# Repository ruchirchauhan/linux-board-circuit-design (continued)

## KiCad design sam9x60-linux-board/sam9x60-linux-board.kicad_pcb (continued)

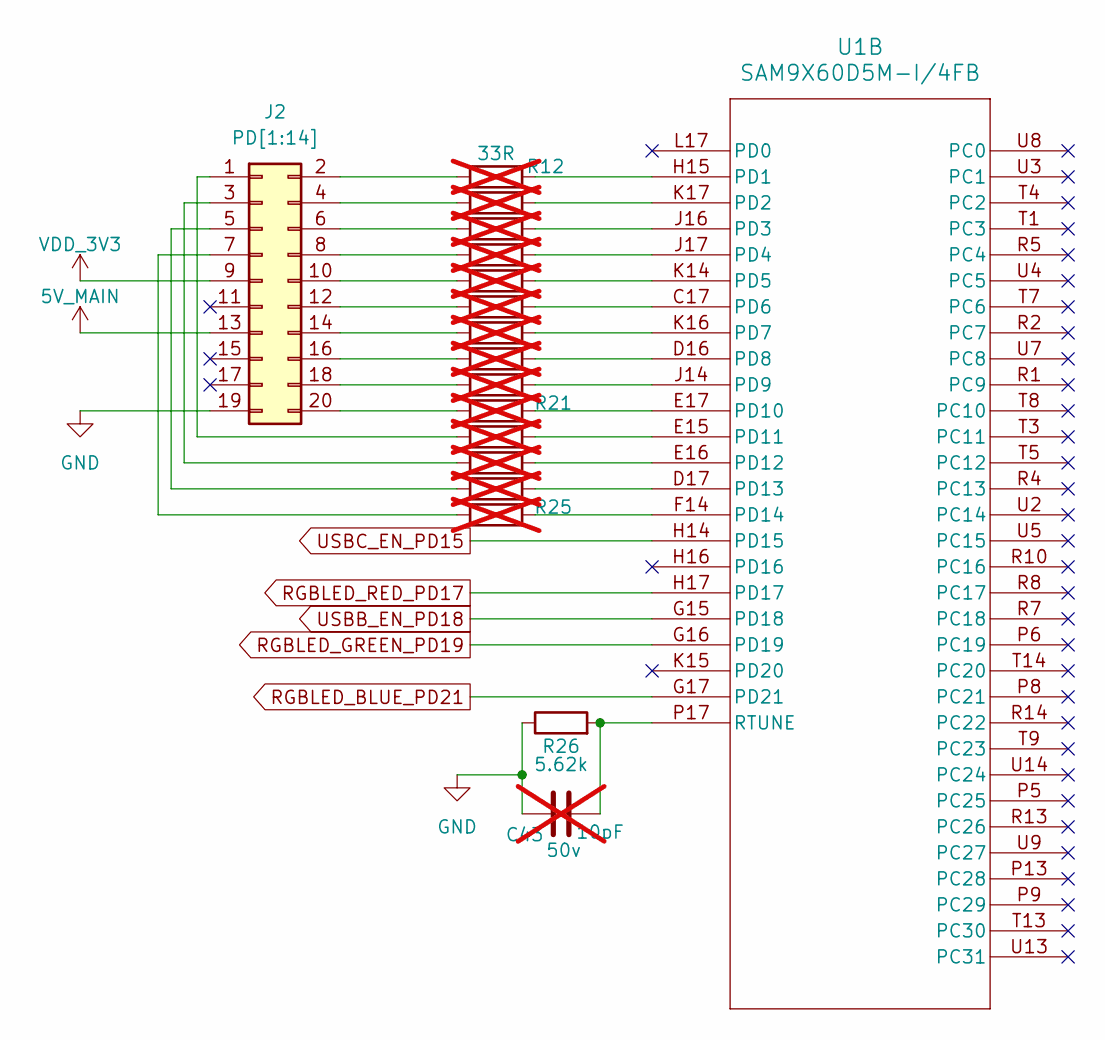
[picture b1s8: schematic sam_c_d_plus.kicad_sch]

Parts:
C43: 10pF; C_0805_2012Metric; Voltage 50v; not fitted
J2: PD[1:14]; PinHeader_2x10_P2.54mm_Vertical
R12, R13, R14, R15, R16, R17, R18, R19, R20, R21, R22, R23, R24, R25: 33R; R_0603_1608Metric; not fitted
R26: 5.62k; R_0603_1608Metric
U1: SAM9X60D5M-I/4FB; TFBGA233_4FB_MCH

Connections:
5V_MAIN: J2.13; also elsewhere on the board
/sam_a_b_plus/DDRCAL: U1.C8 (DDR_CAL); also elsewhere on the board
/sam_a_b_plus/XIN24M: U1.T11 (XIN); also elsewhere on the board
/sam_a_b_plus/XIN32K: U1.U10 (XIN32); also elsewhere on the board
/sam_a_b_plus/XOUT24M: U1.U11 (XOUT); also elsewhere on the board
/sam_a_b_plus/XOUT32K: U1.T10 (XOUT32); also elsewhere on the board
DBGU_RX_PA9: U1.N2 (PA9); also elsewhere on the board
DBGU_TX_PA10: U1.M4 (PA10); also elsewhere on the board
EEPROM_TWCK_PA1: U1.L3 (PA1); also elsewhere on the board
EEPROM_TWD_PA0: U1.L2 (PA0); also elsewhere on the board
ETH0_IRQ_PB8: U1.D5 (PB8); also elsewhere on the board
ETH0_MDC_PB6: U1.D3 (PB6); also elsewhere on the board
ETH0_MDIO_PB5: U1.E1 (PB5); also elsewhere on the board
ETH0_NRST_PB16: U1.E2 (PB16); also elsewhere on the board
ETH0_RX0_PB0: U1.B3 (PB0); also elsewhere on the board
ETH0_RX1_PB1: U1.D1 (PB1); also elsewhere on the board
ETH0_RXDV_PB3: U1.D2 (PB3); also elsewhere on the board
ETH0_RXER_PB2: U1.A3 (PB2); also elsewhere on the board
ETH0_TX0_PB9: U1.B4 (PB9); also elsewhere on the board
ETH0_TX1_PB10: U1.B5 (PB10); also elsewhere on the board
ETH0_TXCK_PB4: U1.E3 (PB4); also elsewhere on the board
ETH0_TXEN_PB7: U1.F4 (PB7); also elsewhere on the board
FCOM1_UART_RX_PA6: U1.N1 (PA6); also elsewhere on the board
FCOM1_UART_TX_PA5: U1.N3 (PA5); also elsewhere on the board
FCOM5_SPI_CK_PA23: U1.C11 (PA23); also elsewhere on the board
FCOM5_SPI_MISO_PA21: U1.B11 (PA21); also elsewhere on the board
FCOM5_SPI_MOSI_PA22: U1.A10 (PA22); also elsewhere on the board
FCOM5_SPI_NPCS0_PA8: U1.P3 (PA8); also elsewhere on the board
FCOM5_SPI_NPCS1_PA7: U1.P2 (PA7); also elsewhere on the board
FCOM5_SPI_NPCS2_PA31: U1.H2 (PA31); also elsewhere on the board
FCOM5_SPI_NPCS3_PA30: U1.H1 (PA30); also elsewhere on the board
FCOM12_I2C_TWCK_PB22: U1.B8 (PB22); also elsewhere on the board
FCOM12_I2C_TWD_PB21: U1.A8 (PB21); also elsewhere on the board
GND: C43.1, J2.19, R26.1, U1.N7 (GNDIN33), U1.P7 (GNDIN33); also elsewhere on the board
MCP16501_LPM_PB15: U1.C4 (PB15); also elsewhere on the board
MPU_NRSTOUT_PB25: U1.B7 (PB25); also elsewhere on the board
NRST: U1.P1 (NRST); also elsewhere on the board
unnamed: J2.1, R22.1
unnamed: J2.2, R12.1
unnamed: J2.3, R23.1
unnamed: J2.4, R13.1
unnamed: J2.5, R24.1
unnamed: J2.6, R14.1
unnamed: J2.7, R25.1
unnamed: J2.8, R15.1
unnamed: J2.10, R16.1
unnamed: J2.12, R17.1
unnamed: J2.14, R18.1
unnamed: J2.16, R19.1
unnamed: J2.18, R20.1
unnamed: J2.20, R21.1
unnamed 76: U1.P11 (VDDOUT25); also elsewhere on the board
unnamed: R12.2, U1.H15 (PD1)
unnamed: R13.2, U1.K17 (PD2)
unnamed: R14.2, U1.J16 (PD3)
unnamed: R15.2, U1.J17 (PD4)
unnamed: R16.2, U1.K14 (PD5)
unnamed: R17.2, U1.C17 (PD6)
unnamed: R18.2, U1.K16 (PD7)
unnamed: R19.2, U1.D16 (PD8)
unnamed: R20.2, U1.J14 (PD9)
unnamed: R21.2, U1.E17 (PD10)
unnamed: R22.2, U1.E15 (PD11)
unnamed: R23.2, U1.E16 (PD12)
unnamed: R24.2, U1.D17 (PD13)
unnamed: R25.2, U1.F14 (PD14)
unnamed: C43.2, R26.2, U1.P17 (RTUNE)
RGBLED_BLUE_PD21: U1.G17 (PD21); also elsewhere on the board
RGBLED_GREEN_PD19: U1.G16 (PD19); also elsewhere on the board
RGBLED_RED_PD17: U1.H17 (PD17); also elsewhere on the board
RTCK: U1.N4 (RTCK); also elsewhere on the board
SDMMC0_CD_PA25: U1.A9 (PA25); also elsewhere on the board
SDMMC0_CK_PA17: U1.H4 (PA17); also elsewhere on the board
SDMMC0_CMD_PA16: U1.J2 (PA16); also elsewhere on the board
SDMMC0_DAT0_PA15: U1.K1 (PA15); also elsewhere on the board
SDMMC0_DAT1_PA18: U1.H3 (PA18); also elsewhere on the board
SDMMC0_DAT2_PA19: U1.J1 (PA19); also elsewhere on the board
SDMMC0_DAT3_PA20: U1.J4 (PA20); also elsewhere on the board
SHDN: U1.N17 (SHDN); also elsewhere on the board
TCK: U1.P12 (TCK); also elsewhere on the board
TDI: U1.L15 (TDI); also elsewhere on the board
TDO: U1.N15 (TDO); also elsewhere on the board
TMS: U1.N16 (TMS); also elsewhere on the board
USBA_N: U1.U16 (HSDMA); also elsewhere on the board
USBA_P: U1.T15 (HSDPA); also elsewhere on the board
USBA_VBUS_DETECT_PA27: U1.D12 (PA27); also elsewhere on the board
USBB_EN_PD18: U1.G15 (PD18); also elsewhere on the board
USBB_N: U1.R17 (HSDMB); also elsewhere on the board
USBB_OVCUR_PA26: U1.D10 (PA26); also elsewhere on the board
USBB_P: U1.T17 (HSDPB); also elsewhere on the board
USBC_EN_PD15: U1.H14 (PD15); also elsewhere on the board
USBC_N: U1.P15 (HSDMC); also elsewhere on the board
USBC_OVCUR_PA28: U1.A11 (PA28); also elsewhere on the board
USBC_P: U1.P16 (HSDPC); also elsewhere on the board
USER_BUTTON_PA29: U1.C10 (PA29); also elsewhere on the board
VDD_3V3: J2.9, U1.N11 (VDDIN33), U1.R12 (VDDIN33); also elsewhere on the board
WAKE_UP: U1.L16 (WKUP0); also elsewhere on the board

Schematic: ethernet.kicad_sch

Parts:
C57, C58, C59, C61, C63, C65: 0.1uF; C_0402_1005Metric_Pad0.74x0.62mm_HandSolder; Voltage 50v
C60: 2.2uF; C_0805_2012Metric; Voltage 16v
C62, C64: 10uF; C_0805_2012Metric; Voltage 10v
FL3, FL4: BLM18PG181SN1D; BEADC1608X95N
J7: ARJM11A1-009-AB-EW2; ARJM11A1-009-AB-EW2_ABR
R54: 330R; R_0603_1608Metric
R55, R61, R62: 10k; R_0603_1608Metric
R56, R58: 0R; R_0603_1608Metric
R57: 6.49K; R_0603_1608Metric
R59, R60: 1k; R_0603_1608Metric
R63, R64: 39R; R_0603_1608Metric
U9: phy-transceiver-KSZ8081RNAIA-TR; ksz8081-phy-transceiver-QFN-24_MCH
Y3: SiT8008BI-11-YYS-25.00; Oscillator_SMD_SiT_PQFN-4Pin_2.5x2.0mm

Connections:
/ethernet/ETH0_CLK: R58.1, Y3.3 (OUT)
/ethernet/ETH0_LED0: J7.9 (ANODE), R61.2, U9.23 (LED0/ANEN_SPEED)
/ethernet/ETH0_RST: R63.1, R64.1, U9.24 (*RST)
/ethernet/ETH0_RX_N: J7.6 (RD-), U9.3 (RXM)
/ethernet/ETH0_RX_P: J7.3 (RD+), U9.4 (RXP)
/ethernet/ETH0_TX_N: J7.2 (TD-), U9.5 (TXM)
/ethernet/ETH0_TX_P: J7.1 (TD+), U9.6 (TXP)
ETH0_IRQ_PB8: R59.2, U9.18 (INTRP); also elsewhere on the board
ETH0_MDC_PB6: U9.11 (MDC); also elsewhere on the board
ETH0_MDIO_PB5: R60.2, U9.10 (MDIO); also elsewhere on the board
ETH0_NRST_PB16: R64.2; also elsewhere on the board
ETH0_RX0_PB0: U9.13 (RXD0); also elsewhere on the board
ETH0_RX1_PB1: U9.12 (RXD1); also elsewhere on the board
ETH0_RXDV_PB3: R62.1, U9.15 (CRS_DV/PHYAD[1:0]); also elsewhere on the board
ETH0_RXER_PB2: U9.17 (RXER); also elsewhere on the board
ETH0_TX0_PB9: U9.20 (TXD0); also elsewhere on the board
ETH0_TX1_PB10: U9.21 (TXD1); also elsewhere on the board
ETH0_TXCK_PB4: U9.16 (REF_CLK/PHYAD[2]); also elsewhere on the board
ETH0_TXEN_PB7: U9.19 (TXEN); also elsewhere on the board
Earth_ETH0: FL3.1, J7.8 (SHLD), J7.13 (SHLD), J7.14 (SHLD)
GND: C57.2, C60.1, C61.1, C62.2, C63.2, C64.2, C65.2, FL3.2, R56.1, R57.1, R62.2, U9.22 (GND), U9.25 (EPAD), Y3.2 (GND); also elsewhere on the board
GND_ETH0: C58.2, C59.2, R56.2
MPU_NRSTOUT_PB25: R63.2; also elsewhere on the board
unnamed: C58.1, J7.5 (CT)
unnamed: C59.1, J7.4 (CT)
unnamed: J7.10 (CATHODE), R54.2
unnamed: R57.2, U9.9 (REXT)
unnamed: C62.1, C63.1, FL4.2, U9.2 (VDDA_3.3)
unnamed: C60.2, C61.2, U9.1 (VDD_1.2)
unnamed: R58.2, U9.8 (XI)
unnamed: R55.2, Y3.1 (~ST)
VDD_3V3: C57.1, C64.1, C65.1, FL4.1, R54.1, R55.1, R59.1, R60.1, R61.1, U9.14 (VDDIO), Y3.4 (Vdd); also elsewhere on the board

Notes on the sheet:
ETH0
DIFF 100
Matched Net Lengths [tolerance=0.5mm]
Differential traces with 100 ohm impedance
50 Ohm single-ended trace impedance

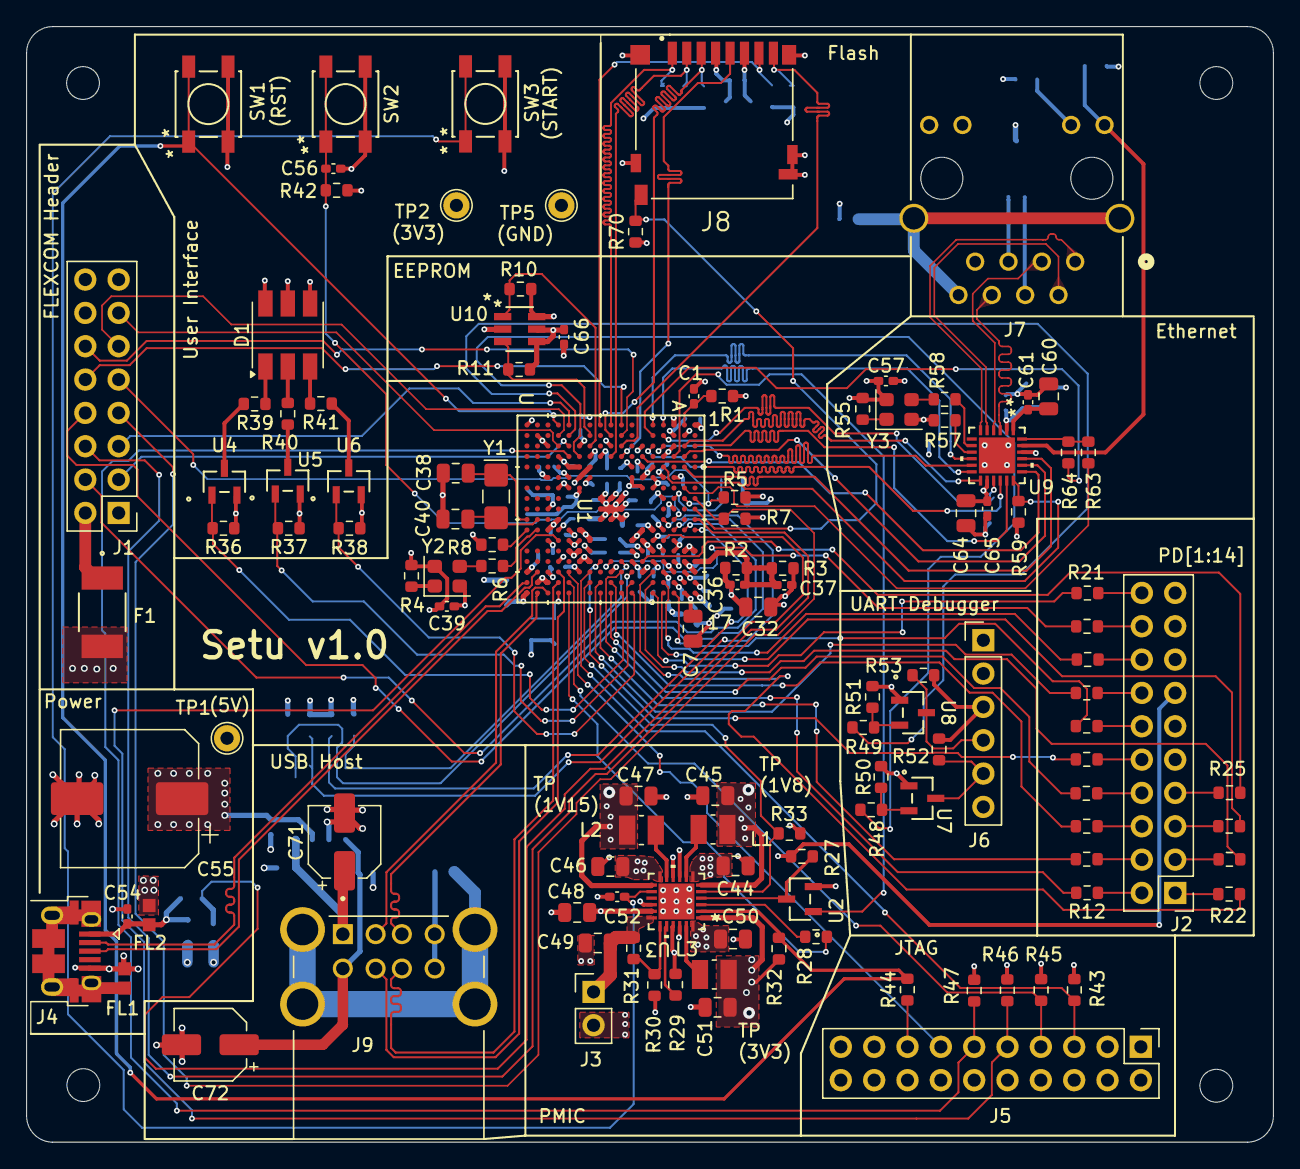
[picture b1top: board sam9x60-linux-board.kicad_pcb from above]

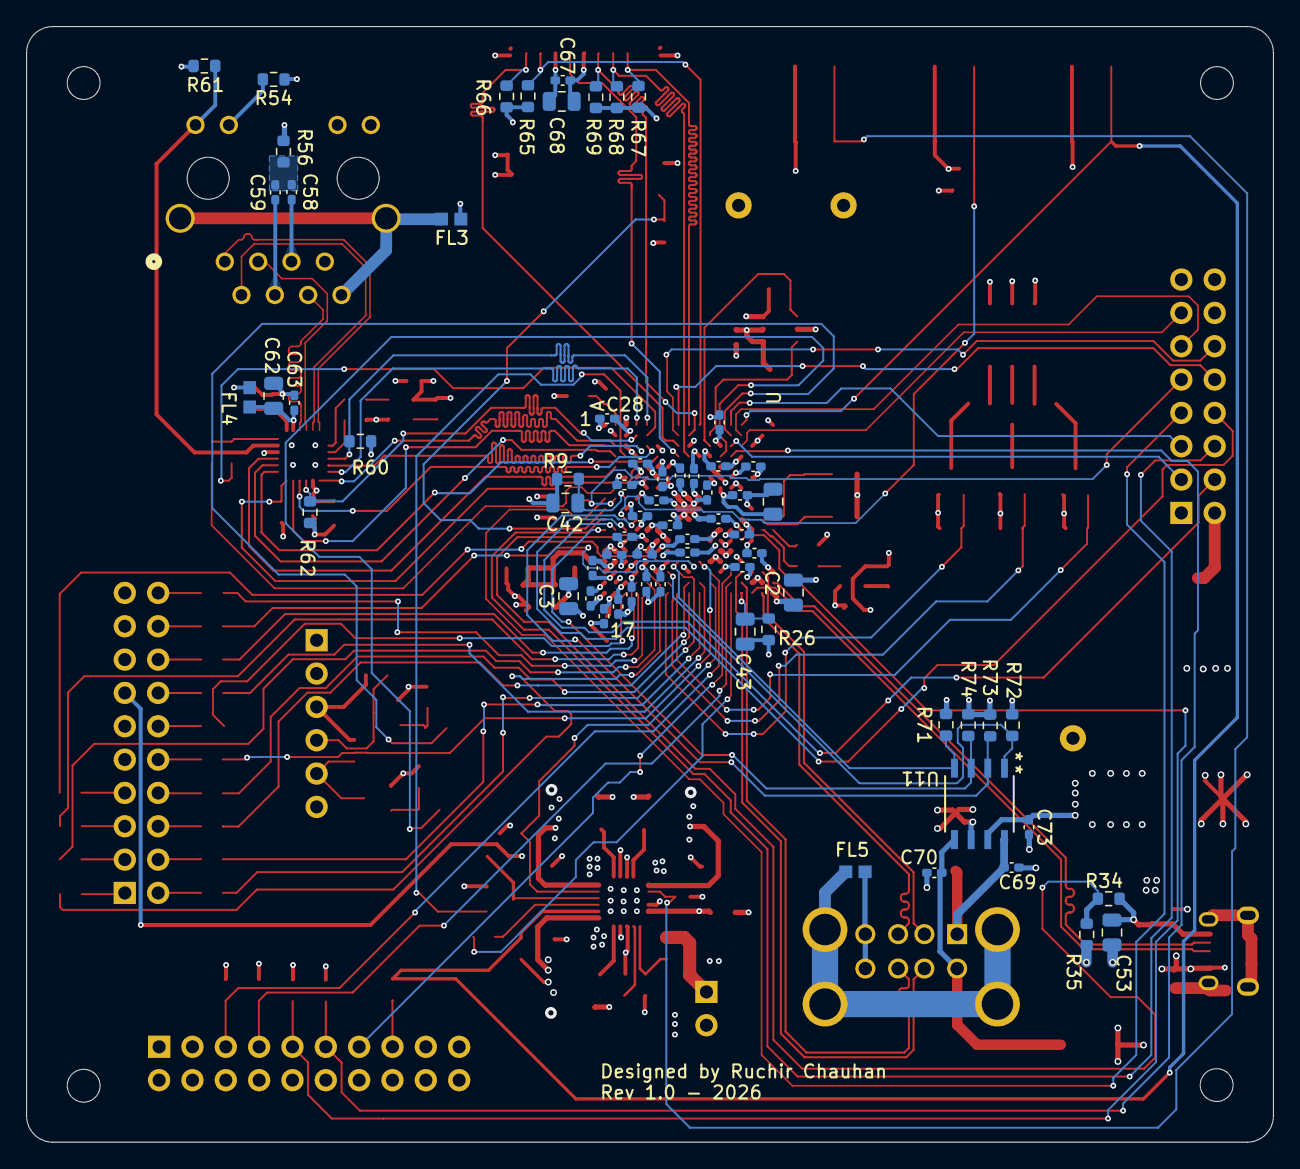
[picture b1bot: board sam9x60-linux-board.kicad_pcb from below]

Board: 4 copper layers, 95.0 x 85.0 mm, 190 parts (67 on the bottom side), 147 nets.

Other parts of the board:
C38: 018pF; C_0805_2012Metric
C39, C41: 0.1uF; C_0402_1005Metric_Pad0.74x0.62mm_HandSolder
C40: 18pF; C_0805_2012Metric
C42: 22pF; C_0805_2012Metric
F1: fuse-1812L200THPR; FUSE_1812L200_LTF
J1: FLEXCOM Header; PinHeader_2x08_P2.54mm_Vertical
R4: 10k; R_0603_1608Metric
R5, R7, R10, R11: 4.7k; R_0603_1608Metric
R6: 33; R_0603_1608Metric
R8: 0; R_0603_1608Metric
R9: 20k; R_0603_1608Metric
REF1, REF2, REF3, REF4: MountingHole_2.5mm
Y1: 32.768 kHz 12pF; Crystal_SMD_G8-2Pin_3.2x1.5mm_HandSoldering
Y2: SiT8008BI-11-YYS-24.00; Oscillator_SMD_SiT_PQFN-4Pin_2.5x2.0mm

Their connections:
5V_MAIN: F1.2; also elsewhere on the board
/sam_a_b_plus/DDRCAL: C42.1, R9.1; also elsewhere on the board
/sam_a_b_plus/XIN24M: R6.2; also elsewhere on the board
/sam_a_b_plus/XIN32K: C38.1, Y1.1; also elsewhere on the board
/sam_a_b_plus/XOUT24M: R8.1; also elsewhere on the board
/sam_a_b_plus/XOUT32K: C40.2, Y1.2; also elsewhere on the board
EEPROM_TWCK_PA1: R10.1; also elsewhere on the board
EEPROM_TWD_PA0: R11.1; also elsewhere on the board
FCOM1_UART_RX_PA6: J1.5; also elsewhere on the board
FCOM1_UART_TX_PA5: J1.3; also elsewhere on the board
FCOM5_SPI_CK_PA23: J1.8; also elsewhere on the board
FCOM5_SPI_MISO_PA21: J1.4; also elsewhere on the board
FCOM5_SPI_MOSI_PA22: J1.6; also elsewhere on the board
FCOM5_SPI_NPCS0_PA8: J1.13; also elsewhere on the board
FCOM5_SPI_NPCS1_PA7: J1.11; also elsewhere on the board
FCOM5_SPI_NPCS2_PA31: J1.12; also elsewhere on the board
FCOM5_SPI_NPCS3_PA30: J1.10; also elsewhere on the board
FCOM12_I2C_TWCK_PB22: J1.9, R5.1; also elsewhere on the board
FCOM12_I2C_TWD_PB21: J1.7, R7.1; also elsewhere on the board
GND: C38.2, C39.2, C40.1, C41.2, C42.2, J1.14, J1.15, J1.16, R8.2, R9.2, Y2.2 (GND); also elsewhere on the board
unnamed: F1.1, J1.2
unnamed 76: C41.1; also elsewhere on the board
unnamed: R6.1, Y2.3 (OUT)
unnamed: R4.2, Y2.1 (~ST)
VDD_3V3: C39.1, J1.1, R4.1, R5.2, R7.2, R10.2, R11.2, Y2.4 (Vdd); also elsewhere on the board
